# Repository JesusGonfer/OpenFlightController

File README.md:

# Open FC

### Hardware
  - STM32F405RGT6
  - MPU6000
  - MAX7456 OSD
  - 5v regulator
  - 3v3 regulator
  - 4 motor ouput
  - 30.5*30.5 mount hole
  - SoftMount FC

### Firmware
  - [Betaflight](https://github.com/betaflight/betaflight)
  - [Inav](https://github.com/iNavFlight/inav)

## What is Open FC?
Open fc is an attempt to create a homemade fc, compatible with betaflight and inav, and listening to the opinions of everyone who wants to contribute something. If your opinion is not implemented, feel free to fork this repository.
This project is not a high priority so it will not be completed in the short term, thanks for your understanding.

## License

[ <br> Creative Commons](https://creativecommons.org/licenses/by-sa/4.0/)

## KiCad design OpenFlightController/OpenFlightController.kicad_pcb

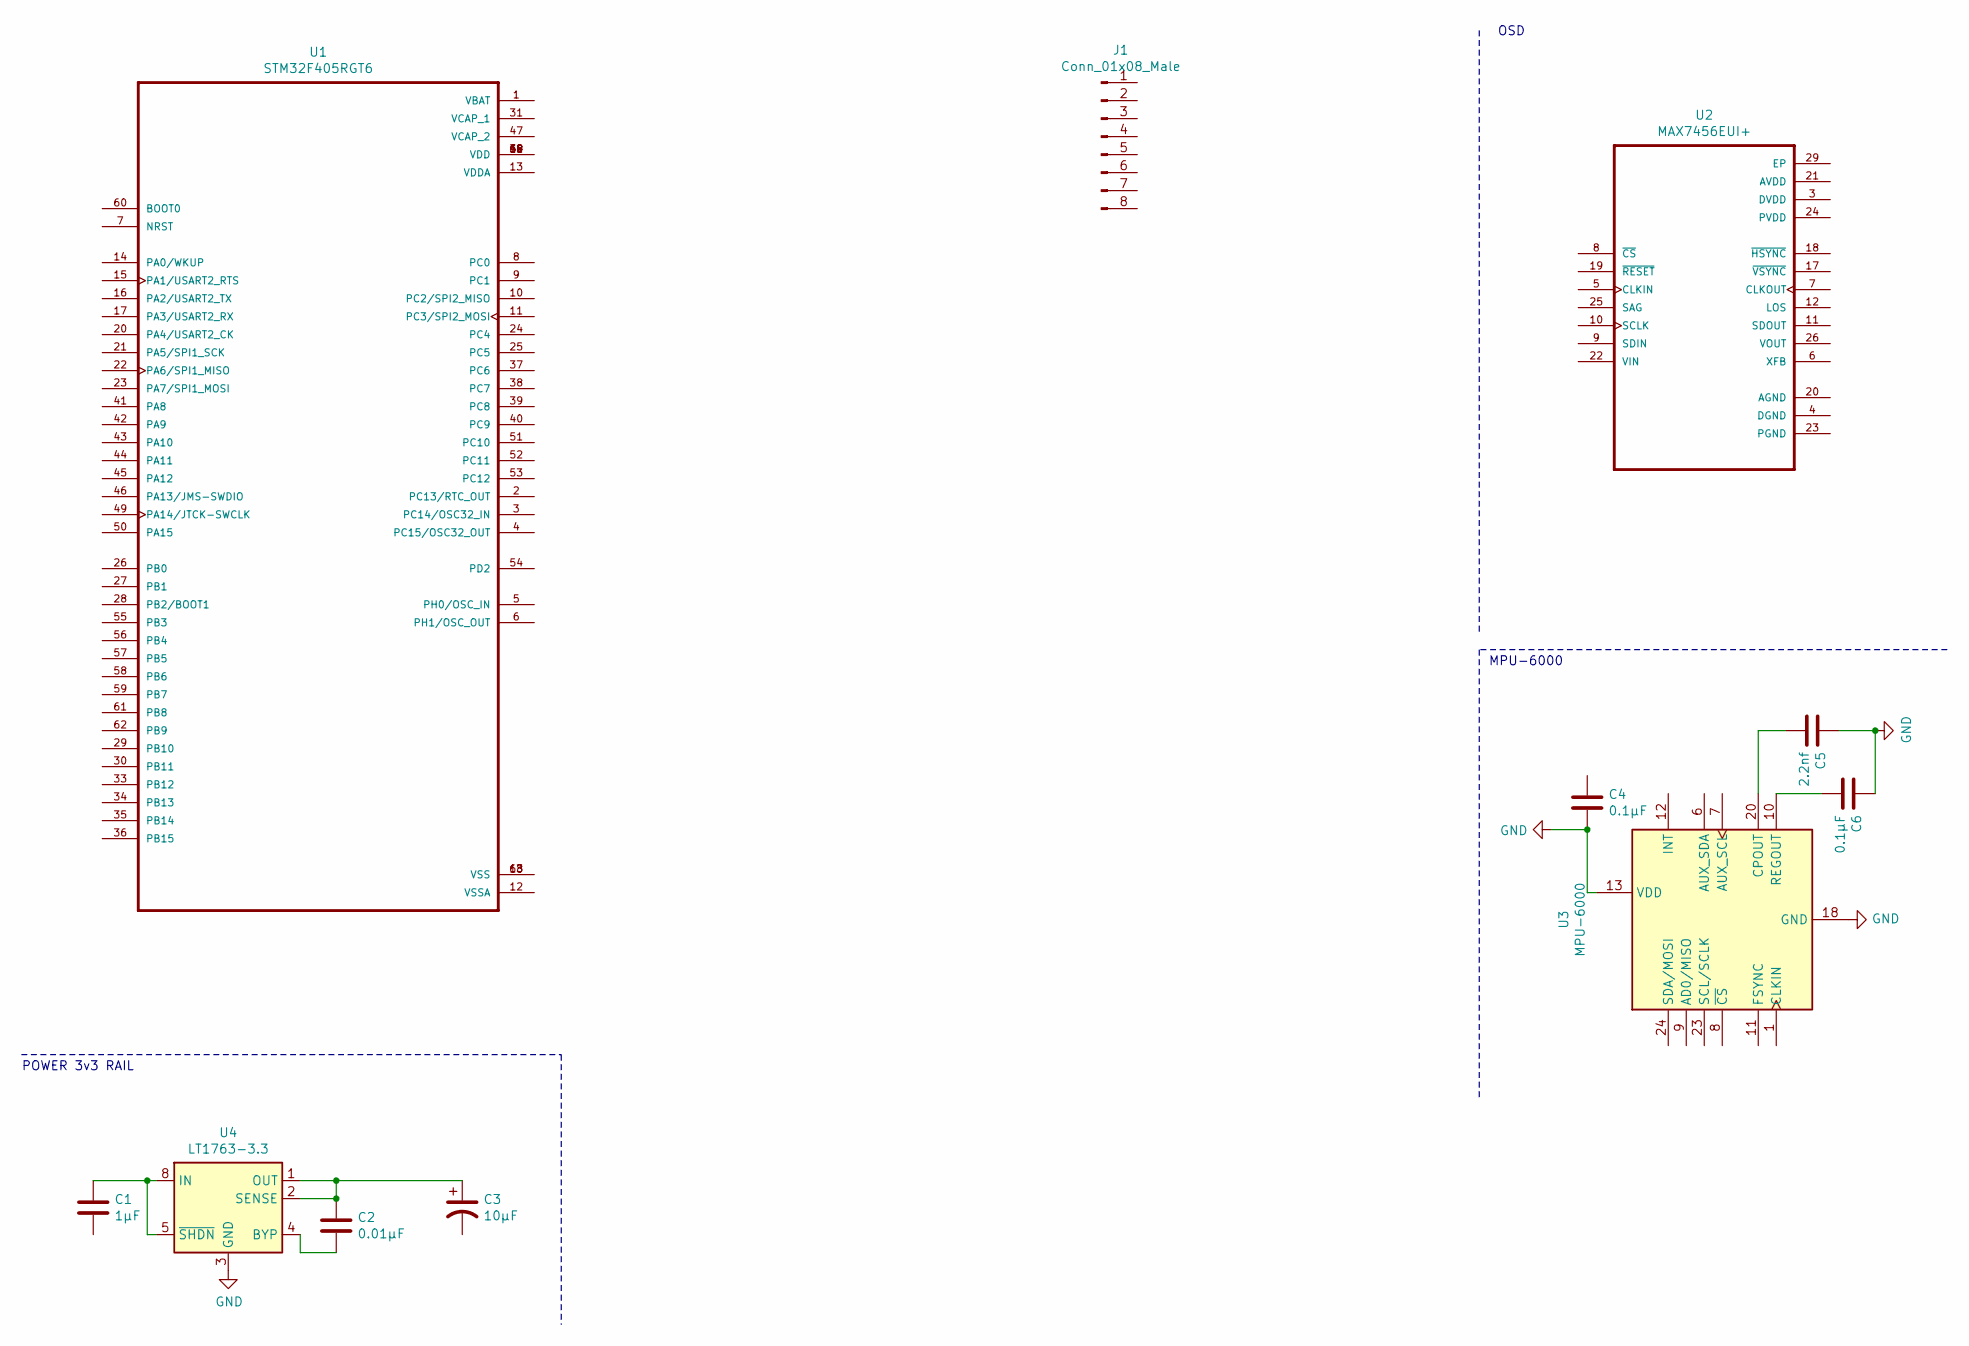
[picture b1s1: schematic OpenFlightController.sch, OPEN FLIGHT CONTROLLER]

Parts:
C1: 1µF; C_0603_1608Metric
C2: 0.01µF; C_0603_1608Metric
C3: 10µF
C4, C6: 0.1µF; C_0603_1608Metric
C5: 2.2nf; C_0603_1608Metric
J1: Conn_01x08_Male; JST_GH_SM08B-GHS-TB_1x08-1MP_P1.25mm_Horizontal
U1: STM32F405RGT6; MAX7456
U2: MAX7456EUI+; MAX7456
U3: MPU-6000; InvenSense_QFN-24_4x4mm_P0.5mm
U4: LT1763-3.3; SOP-8_3.76x4.96mm_P1.27mm

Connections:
GND: C4.2, C5.1, C6.1, U3.13 (VDD), U3.18 (GND), U4.3 (GND)
unnamed: C1.1, U4.5 (~SHDN), U4.8 (IN)
unnamed: C2.1, C3.1, U4.1 (OUT), U4.2 (SENSE)
unnamed: C2.2, U4.4 (BYP)
unnamed: C5.2, U3.20 (CPOUT)
unnamed: C6.2, U3.10 (REGOUT)
unnamed: U1.18 (VSS), U1.63 (VSS)
unnamed: U1.19 (VDD), U1.32 (VDD), U1.48 (VDD), U1.64 (VDD)

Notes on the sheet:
POWER 3v3 RAIL
MPU-6000
OSD

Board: 2 copper layers, 10 parts (0 on the bottom side), 8 nets, no tracks yet.

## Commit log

2020-02-05 Create empty kicad project
2020-02-05 EdgeCuts PCB 0.1v
2020-02-13 Updated License
2020-02-13 Add Power In 3v3
